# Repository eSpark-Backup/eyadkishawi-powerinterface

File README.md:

# Power and Interface Board Design
#### Client Name: Eyad Kishawi

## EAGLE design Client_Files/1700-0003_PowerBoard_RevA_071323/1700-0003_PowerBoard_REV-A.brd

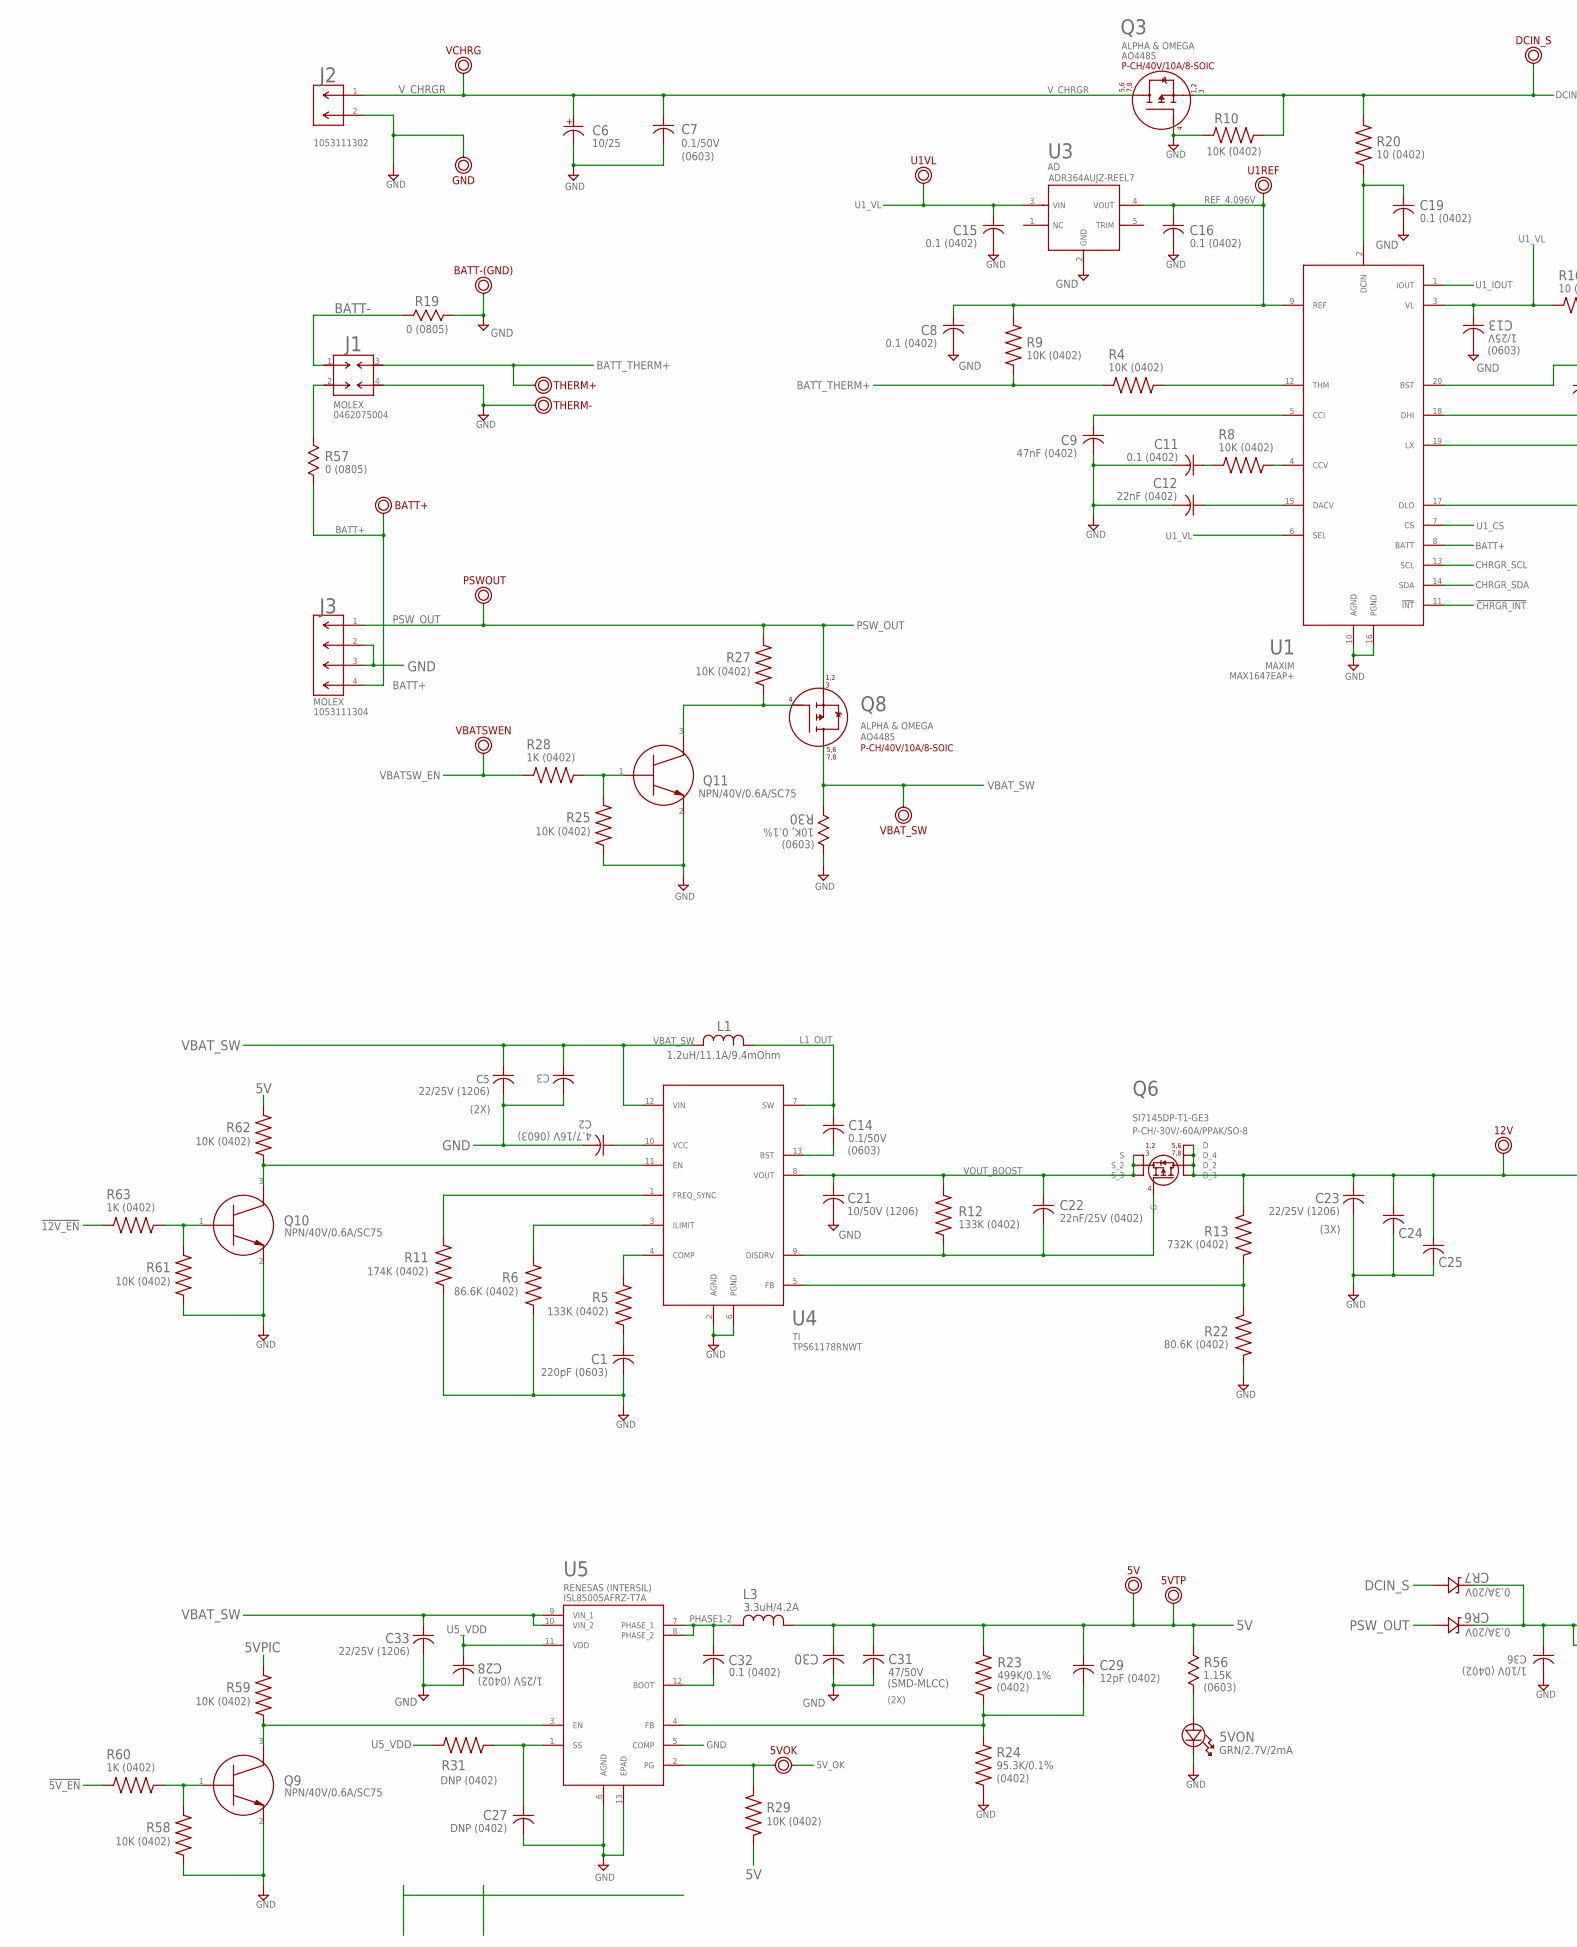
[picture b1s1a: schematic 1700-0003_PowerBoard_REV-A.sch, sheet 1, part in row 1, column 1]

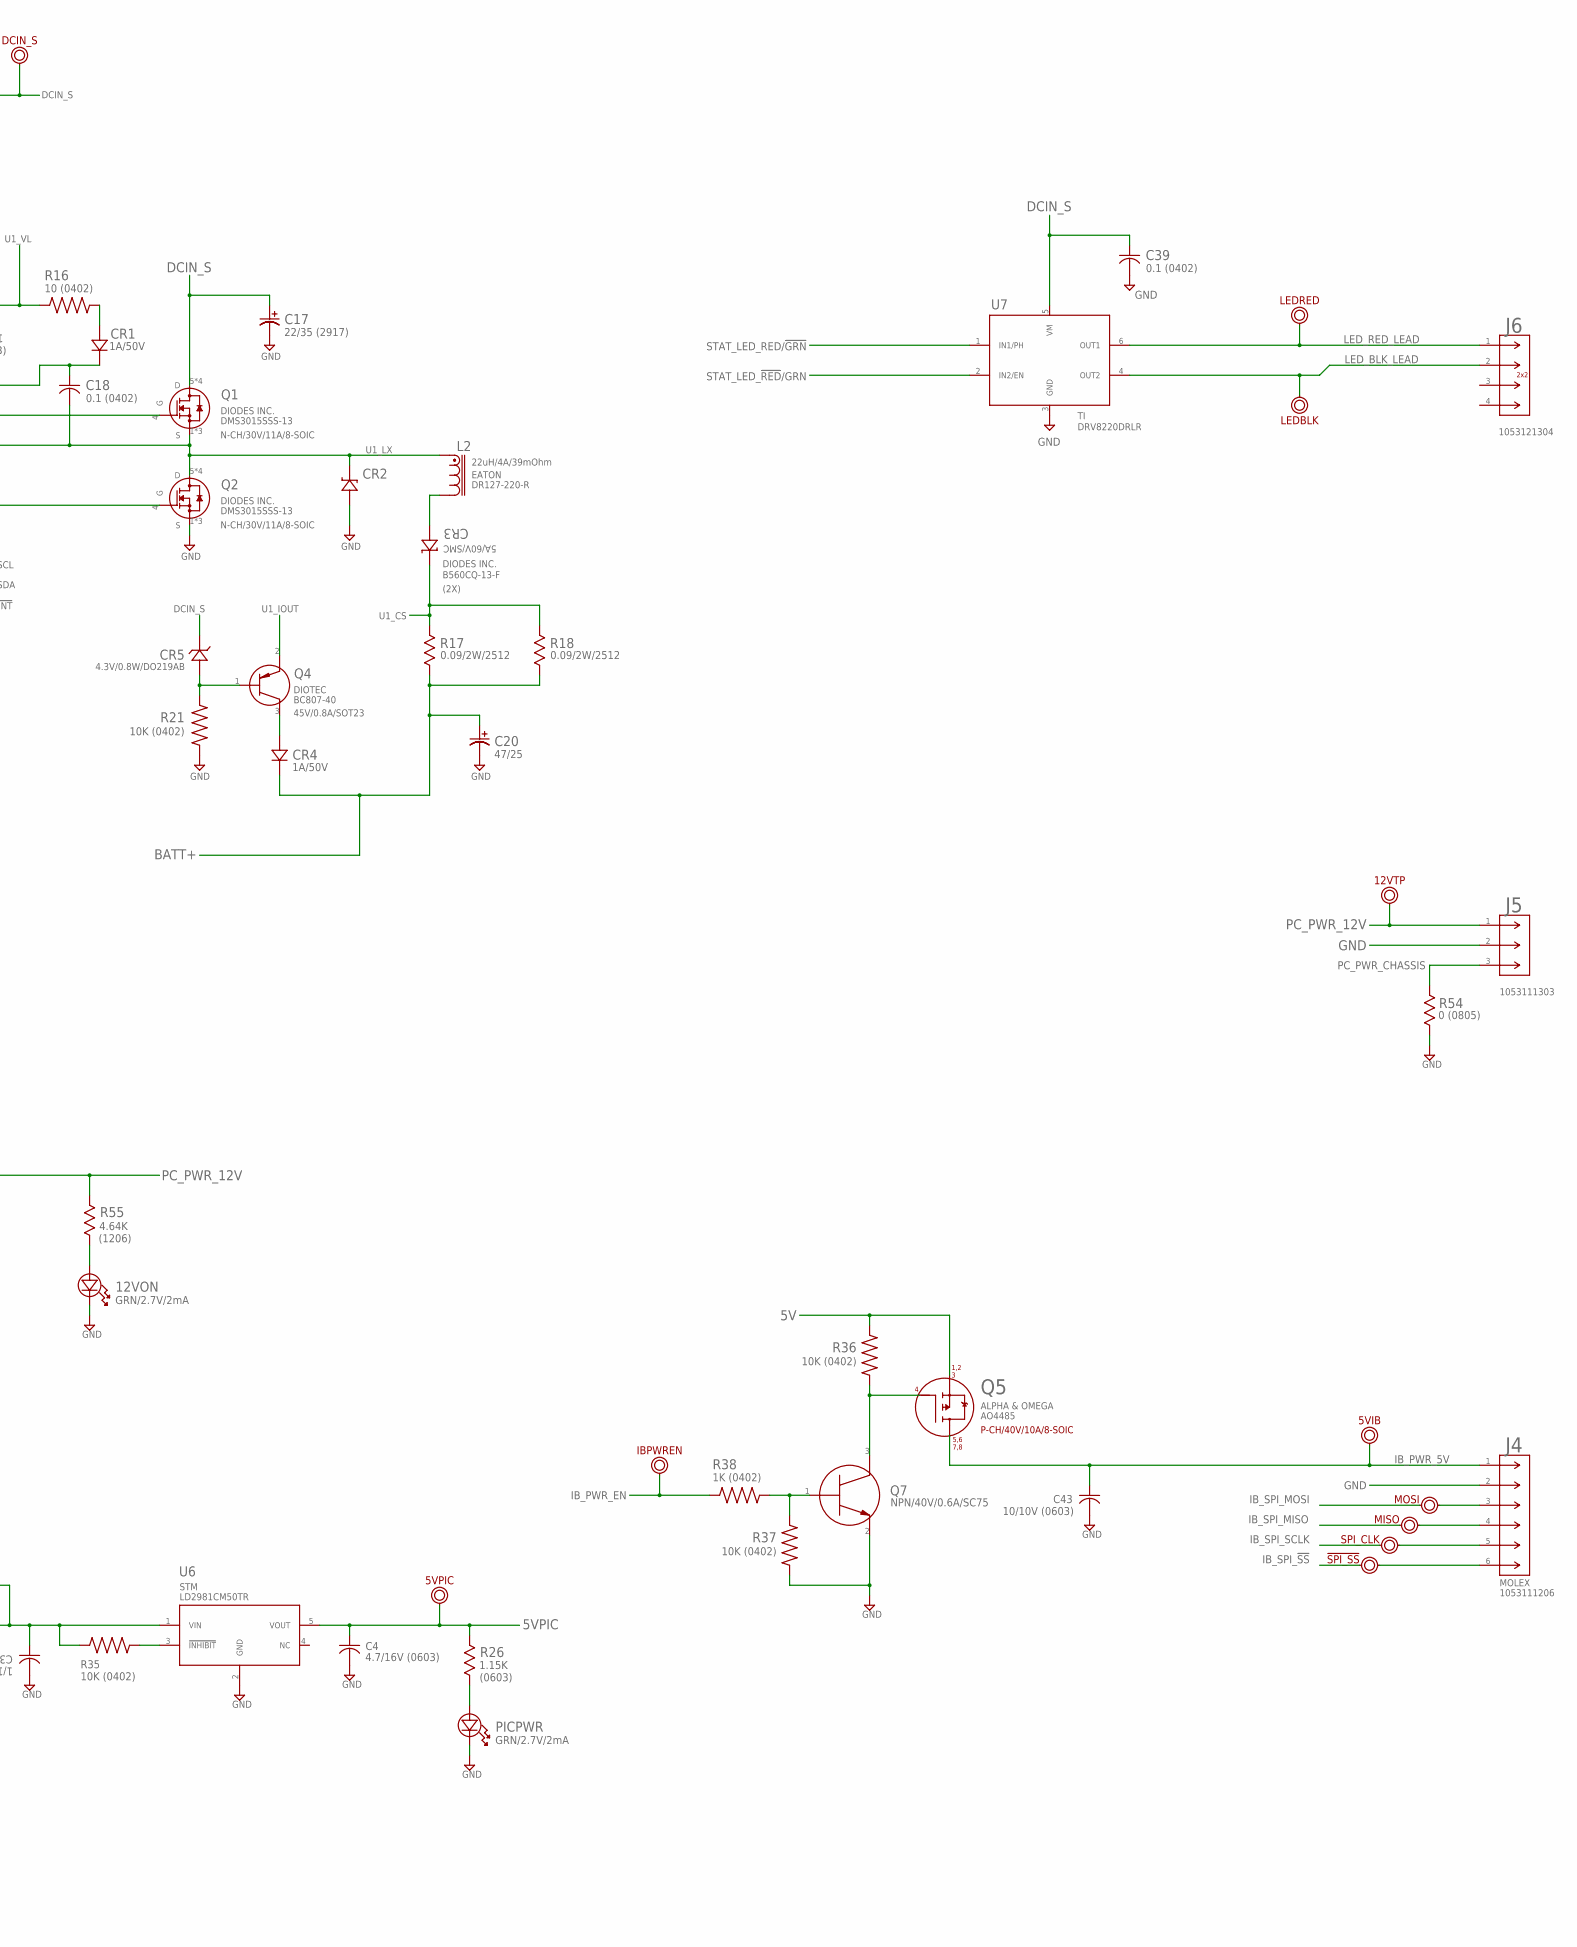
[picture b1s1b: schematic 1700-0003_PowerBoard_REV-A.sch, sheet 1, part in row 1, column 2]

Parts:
5V, 5VPIC, 12V: TST_POINT_PTH_042-OCT
5VIB, 5VTP, 12VTP: TST_POINT_PTH_20X40MIL
5VOK: TST_POINT_PTH_20X40MIL_2PIN
5VON, 12VON: GRN/2.7V/2mA; LED_DIALIGHT_598_DIA
!SPI_SS!: TST_POINT_PTH_042_2PIN; TST_POINT_PTH_042-OCT_2PIN; PART_DESC PCB feature, test point, ID 42mil, OD 7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
BATT+: TST_POINT_PTH_042-OCT
BATT-(GND): TST_POINT_PTH_042-OCT
C1: 220pF (0603); CAP_C1608_TDK; MANUFACTURER_PART_NUMBER CL10C221JB8NNNC
C2, C4: 4.7/16V (0603); CAP_C1608_TDK; MANUFACTURER_PART_NUMBER GRM188Z71C475KE21D
C3, C5, C33: 22/25V (1206); CAP_CL31_SAM
C6: 10/25; CAP_AFK106M25B12T-F_CND-L
C7, C14: 0.1/50V; CAP_C1608_TDK; MANUFACTURER_PART_NUMBER CL10B104KB8NNNC
C8, C11, C15, C16, C18, C19, C32, C39: 0.1 (0402); G-155_MUR
C9: 47nF (0402); G-155_MUR; MANUFACTURER_PART_NUMBER C0402C473K3REC7867
C12: 22nF (0402); G-155_MUR; MANUFACTURER_PART_NUMBER C0402C223K5REC7411
C13: 1/25V; CAP_C1608_TDK; MANUFACTURER_PART_NUMBER CL10B105KA8NNNC
C17: 22/35 (2917); CAPMP7.6X4.3_3.1N_KEM
C20: 47/25; CAPMP7.6X4.3_3.1N_KEM
C21: 10/50V (1206); CAP_CL31_SAM; MANUFACTURER_PART_NUMBER CL31B106KBHNNNE
C22: 22nF/25V (0402); G-155_MUR; MANUFACTURER_PART_NUMBER GRM155R71E223KA61D
C23, C24, C25: 22/25V (1206); CAP_CL31_SAM; MANUFACTURER_PART_NUMBER GCM31CC81E226KE11L
C27: DNP (0402); G-155_MUR; PART_DESC --- DO NOT POPULATE ---
C28: 1/25V (0402); G-155_MUR; MANUFACTURER_PART_NUMBER GRM155R61E105KA12D
C29: 12pF (0402); G-155_MUR; MANUFACTURER_PART_NUMBER C0402C120K5RAC7867
C30: 47/50V (MLCC-SMD); CAP_CKG57N_TDK
C31: 47/50V; CAP_CKG57N_TDK
C36: 1/10V (0402); G-155_MUR; MANUFACTURER_PART_NUMBER GRM155C81C225ME15D
C43: 10/10V (0603); CAP_C1608_TDK; MANUFACTURER_PART_NUMBER GRM188D71A106KA73D
CR1, CR4: 1A/50V; SMA_DIO
CR2, CR3: 5A/60V/SMC; CR_0CQ-13-F_DIO
CR5: 4.3V/0.8W/DO219AB; DIO_BZD27C4V3P_VIS
CR6, CR7: 0.3A/20V; USC_TOS
DCIN_S: TST_POINT_PTH_042-OCT
GND: TST_POINT_PTH_042-OCT
IBPWREN: TST_POINT_PTH_042-OCT
J1: MOLEX_MINI-FIT-JR_462075004; MOLEX_462075004
J2: MOLEX_NANO-FIT_1053111302; CON_1053111302_MOL
J3: MOLEX_NANO-FIT_1053111304; CON_1053111304_MOL
J4: MOLEX_1053111206; CON_1053111206_MOL
J5: MOLEX_NANO-FIT_1053111303; CON_1053111303_MOL
J6: CON_MOLEX_NANOFIT_1053121304; CON_1053121304
L1: 1.2uH/11.1A/9.4mOhm; IND_XAL50XX_COC
L2: 22uH/4A/39mOhm; DR127
L3: 3.3uH/4.2A; IND_CB_DRA74
LEDBLK: TST_POINT_PTH_20X40MIL
LEDRED: TST_POINT_PTH_20X40MIL
MISO: TST_POINT_PTH_042_2PIN; TST_POINT_PTH_042-OCT_2PIN; PART_DESC PCB feature, test point, ID 42mil, OD 7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
MOSI: TST_POINT_PTH_042_2PIN; TST_POINT_PTH_042-OCT_2PIN; PART_DESC PCB feature, test point, ID 42mil, OD 7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
PICPWR: GRN/2.7V/2mA; LED_DIALIGHT_598_DIA
PSWOUT: TST_POINT_PTH_042-OCT
Q1, Q2: N-CH/30V/11A/8-SOIC; SOIC127P600X175-8N
Q3, Q5, Q8: P-CH/40V/10A/8-SOIC; SOIC127P600X175-8N
Q4: 45V/0.8A/SOT23; SOT-23-3_DIOTEC
Q6: P-CH/-30V/-60A/PPAK/SO-8; SON8_SI7135DP-T1-GE3_VIS
Q7, Q9, Q10, Q11: NPN/40V/0.6A/SC75; SC-75(SOT-416)_ONSEMI
R4, R8, R9, R10, R21, R25, R27, R29, R35, R36, R37, R58, R59, R61, R62: 10K (0402); RESC1005X35N
R5: 133K (0402); RESC1005X35N; MANUFACTURER_PART_NUMBER RMCF0402FT133K
R6: 86.6K (0402); RESC1005X35N; MANUFACTURER_PART_NUMBER CPF0402B86K6E1
R11: 174K (0402); RESC1005X35N; MANUFACTURER_PART_NUMBER CRCW0402174KFKTD
R12: 133K (0402); RESC1005X35N; MANUFACTURER_PART_NUMBER RC0402FR-07178KL
R13: 732K (0402); RESC1005X35N; MANUFACTURER_PART_NUMBER CRCW0402732KFKED
R16, R20: 10 (0402); RESC1005X35N; MANUFACTURER_PART_NUMBER CRCW040210R0FKEDC
R17, R18: 0.09/2W/2512; RES_2512_TECONN
R19, R54, R57: 0 (0805); STA_HCJ0805_STP
R22: 80.6K (0402); RESC1005X35N; MANUFACTURER_PART_NUMBER CRCW040280K6FKED
R23: 499K/0.1%; RESC1005X35N; MANUFACTURER_PART_NUMBER MCS0402MD4993BE000
R24: 95.3K/0.1%; RESC1005X35N; MANUFACTURER_PART_NUMBER TNPW040295K3BEED
R26, R56: 1.15K; STA_RMCF0603_STP; MANUFACTURER_PART_NUMBER RMCF0603FT1K15
R28, R38, R60, R63: 1K (0402); RESC1005X35N; MANUFACTURER_PART_NUMBER CRCW04021K00FKEDC
R30: 10K, 0.1%; STA_RMCF0603_STP; MANUFACTURER_PART_NUMBER RNCS0603BKE10K0
R31: DNP (0402); RESC1005X35N; MANUFACTURER_PART_NUMBER ---
R55: 4.64K; RC1206N_YAG; MANUFACTURER_PART_NUMBER CRCW12064K64FKEAC
SPI_CLK: TST_POINT_PTH_042_2PIN; TST_POINT_PTH_042-OCT_2PIN; PART_DESC PCB feature, test point, ID 42mil, OD 7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
THERM+: TST_POINT_PTH_042-OCT
THERM-: TST_POINT_PTH_042-OCT
U1: MAX1647EAP+; 21-0056C_20_MXM; PART_DESC IC BATT CHG MULTI-CHEM 20SSOP
U1REF, U1VL: TST_POINT_PTH_20X40MIL
U3: AD_REFERENCE_ADR364AUJZ-REEL7; UJ_5_ADI
U4: REGULATOR_BOOST_TI_TPS61178RNWT; RNW0013A
U5: REGULATOR_BUCK_RENESAS_ISL85005AFRZ-T7A; SON50P300X400X90-13N; PART_DESC Buck Switching Regulator IC Positive Ad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
U6: IC_LDO_STM_LD2981CM50TR; SOT23-5L_STM
U7: IC_H-BRIDGE_TI_DRV8220DRLR; SOT5X3-6_DRL_TEX
VBATSWEN: TST_POINT_PTH_042-OCT
VBAT_SW: TST_POINT_PTH_042-OCT
VCHRG: TST_POINT_PTH_042-OCT; PART_DESC PCB feature, test point, ID 42mil, OD 7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

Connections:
5V: 5V.P$1, 5VTP.P$1, C29.1, C30.1, C31.1, L3.1, Q5.1 (S), Q5.2 (S), Q5.3 (S), R23.1, R29.1, R36.2, R56.2, R62.2; also elsewhere on the board
5VPIC: 5VPIC.P$1, C4.1, R26.2, R59.2, U6.5 (VOUT); also elsewhere on the board
5V_OK: 5VOK.P$1, 5VOK.P$2, R29.2, U5.2 (PG); also elsewhere on the board
!5V_EN!: R60.1; also elsewhere on the board
!12V_EN!: R63.1; also elsewhere on the board
!CHRGR_INT!: U1.11 (!INT); also elsewhere on the board
$N36: C36.1, CR6.1 (K), CR7.1 (K), R35.2, U6.1 (VIN)
$N99: J1.2, R57.2
BATT+: BATT+.P$1, C20.1, CR4.1, J3.4, R17.2, R18.2, R57.1, U1.8 (BATT)
BATT-: J1.1, R19.2
BATT_THERM+: J1.3, R4.1, R9.2, THERM+.P$1
CHRGR_SCL: U1.13 (SCL); also elsewhere on the board
CHRGR_SDA: U1.14 (SDA); also elsewhere on the board
DCIN_S: C17.1, C39.1, CR5.2 (K), CR7.2 (A), DCIN_S.P$1, Q1.5 (D), Q1.6 (D), Q1.7 (D), Q1.8 (D), Q3.1 (S), Q3.2 (S), Q3.3 (S), R10.2, R20.2, U7.5 (VM); also elsewhere on the board
GND: 5VON.1, 12VON.1, BATT-(GND).P$1, C1.2, C2.2, C3.2, C4.2, C5.2, C6.2, C7.2, C8.2, C9.2, C11.2, C12.2, C13.2, C15.2, C16.2, C17.2, C19.2, C20.2, C21.2, C23.2, C24.2, C25.2, C27.2, C28.2, C30.2, C31.2, C33.2, C36.2, C39.2, C43.2, CR2.1 (A), GND.P$1, J1.4, J2.2, J3.2, J3.3, J4.2, J5.2, PICPWR.1, Q2.1 (S), Q2.2 (S), Q2.3 (S), Q3.4 (G), Q7.2 (E), Q9.2 (E), Q10.2 (E), Q11.2 (E), R6.2, R10.1, R11.2, R19.1, R21.2, R22.2, R24.2, R25.1, R30.2, R37.1, R54.2, R58.1, R61.1, THERM-.P$1, U1.10 (AGND), U1.16 (PGND), U3.2 (GND), U4.2 (AGND), U4.6 (PGND), U5.5 (COMP), U5.6 (AGND), U5.13 (EPAD), U6.2 (GND), U7.3 (GND); also elsewhere on the board
IB_PWR_5V: 5VIB.P$1, C43.1, J4.1, Q5.5 (D), Q5.6 (D), Q5.7 (D), Q5.8 (D)
IB_PWR_EN: IBPWREN.P$1, R38.1; also elsewhere on the board
IB_SPI_!SS: !SPI_SS!.P$1, !SPI_SS!.P$2, J4.6; also elsewhere on the board
IB_SPI_MISO: J4.4, MISO.P$1, MISO.P$2; also elsewhere on the board
IB_SPI_MOSI: J4.3, MOSI.P$1, MOSI.P$2; also elsewhere on the board
IB_SPI_SCLK: J4.5, SPI_CLK.P$1, SPI_CLK.P$2; also elsewhere on the board
L1_OUT: C14.1, L1.1, U4.7 (SW)
LED_BLK_LEAD: J6.2, LEDBLK.P$1, U7.4 (OUT2)
LED_RED_LEAD: J6.1, LEDRED.P$1, U7.6 (OUT1)
unnamed: R5.1, U4.4 (COMP)
unnamed: C19.1, R20.1, U1.2 (DCIN)
unnamed: Q1.4 (G), U1.18 (DHI)
unnamed: C1.1, R5.2
unnamed: R4.2, U1.12 (THM)
unnamed: R6.1, U4.3 (ILIMIT)
unnamed: C2.1, U4.10 (VCC)
unnamed: R11.1, U4.1 (FREQ_SYNC)
unnamed: C9.1, U1.5 (CCI)
unnamed: R8.2, U1.4 (CCV)
unnamed: C11.1, R8.1
unnamed: C12.1, U1.15 (DACV)
unnamed: CR4.2, Q4.3 (C)
unnamed: CR1.2, R16.2
unnamed: Q2.4 (G), U1.17 (DLO)
unnamed: C18.1, CR1.1, U1.20 (BST)
unnamed: CR3.1 (A), L2.2
unnamed: C14.2, U4.13 (BST)
unnamed: C22.2, Q6.4 (G), R12.2, U4.9 (DISDRV)
unnamed: CR5.1 (A), Q4.1 (B), R21.1
unnamed: Q8.4 (G), Q11.3 (C), R27.1
unnamed: C27.1, R31.2, U5.1 (SS)
unnamed: R13.2, R22.1, U4.5 (FB)
unnamed: C32.2, U5.12 (BOOT)
unnamed: C29.2, R23.2, R24.1, U5.4 (FB)
unnamed: 5VON.2, R56.1
unnamed: R35.1, U6.3 (!INHIBIT!)
unnamed: Q11.1 (B), R25.2, R28.2
unnamed: Q5.4 (G), Q7.3 (C), R36.1
unnamed: Q7.1 (B), R37.2, R38.2
unnamed: 12VON.2, R55.2
unnamed: PICPWR.2, R26.1
unnamed: Q9.1 (B), R58.2, R60.2
unnamed: Q9.3 (C), R59.1, U5.3 (EN)
unnamed: Q10.3 (C), R62.1, U4.11 (EN)
unnamed: Q10.1 (B), R61.2, R63.2
PC_PWR_12V: 12V.P$1, 12VTP.P$1, C23.1, C24.1, C25.1, J5.1, Q6.5 (D_3), Q6.6 (D_2), Q6.7 (D_4), Q6.8 (D), R13.1, R55.1; also elsewhere on the board
PC_PWR_CHASSIS: J5.3, R54.1
PHASE1-2: C32.1, L3.2, U5.7 (PHASE_1), U5.8 (PHASE_2)
PSW_OUT: CR6.2 (A), J3.1, PSWOUT.P$1, Q8.1 (S), Q8.2 (S), Q8.3 (S), R27.2; also elsewhere on the board
REF_4.096V: C8.1, C16.1, R9.1, U1.9 (REF), U1REF.P$1, U3.4 (VOUT)
STAT_LED_!RED!/GRN: U7.2 (IN2/EN); also elsewhere on the board
STAT_LED_RED/!GRN!: U7.1 (IN1/PH); also elsewhere on the board
U1_CS: CR3.2 (K), R17.1, R18.1, U1.7 (CS)
U1_IOUT: Q4.2 (E), U1.1 (IOUT)
U1_LX: C18.2, CR2.2 (K), L2.1, Q1.1 (S), Q1.2 (S), Q1.3 (S), Q2.5 (D), Q2.6 (D), Q2.7 (D), Q2.8 (D), U1.19 (LX)
U1_VL: C13.1, C15.1, R16.1, U1.3 (VL), U1.6 (SEL), U1VL.P$1, U3.3 (VIN)
U5_VDD: C28.1, R31.1, U5.11 (VDD)
VBATSW_EN: R28.1, VBATSWEN.P$1; also elsewhere on the board
VBAT_SW: C3.1, C5.1, C33.1, L1.2, Q8.5 (D), Q8.6 (D), Q8.7 (D), Q8.8 (D), R30.1, U4.12 (VIN), U5.9 (VIN_1), U5.10 (VIN_2), VBAT_SW.P$1
VOUT_BOOST: C21.1, C22.1, Q6.1 (S_3), Q6.2 (S_2), Q6.3 (S), R12.1, U4.8 (VOUT)
V_CHRGR: C6.1, C7.1, J2.1, Q3.5 (D), Q3.6 (D), Q3.7 (D), Q3.8 (D), VCHRG.P$1

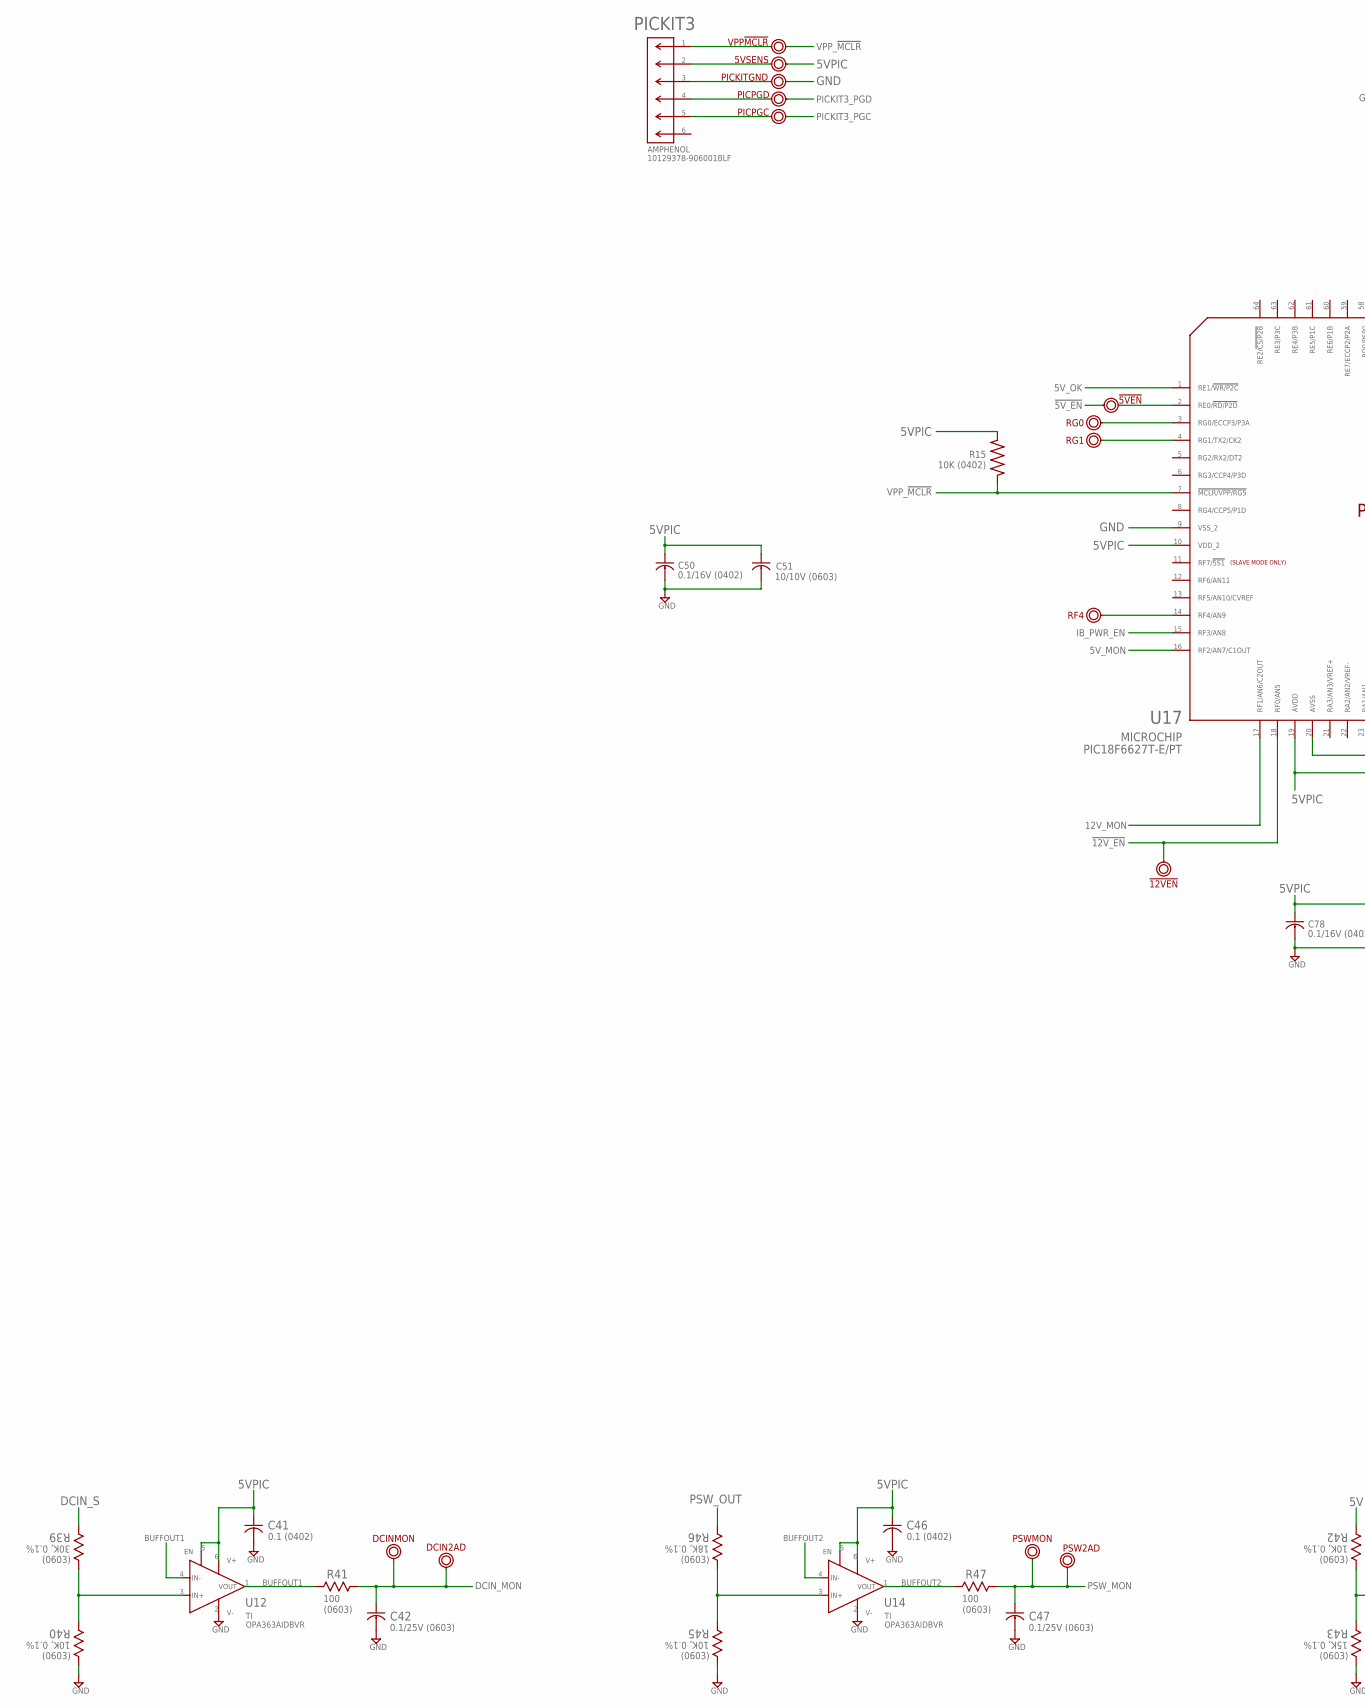
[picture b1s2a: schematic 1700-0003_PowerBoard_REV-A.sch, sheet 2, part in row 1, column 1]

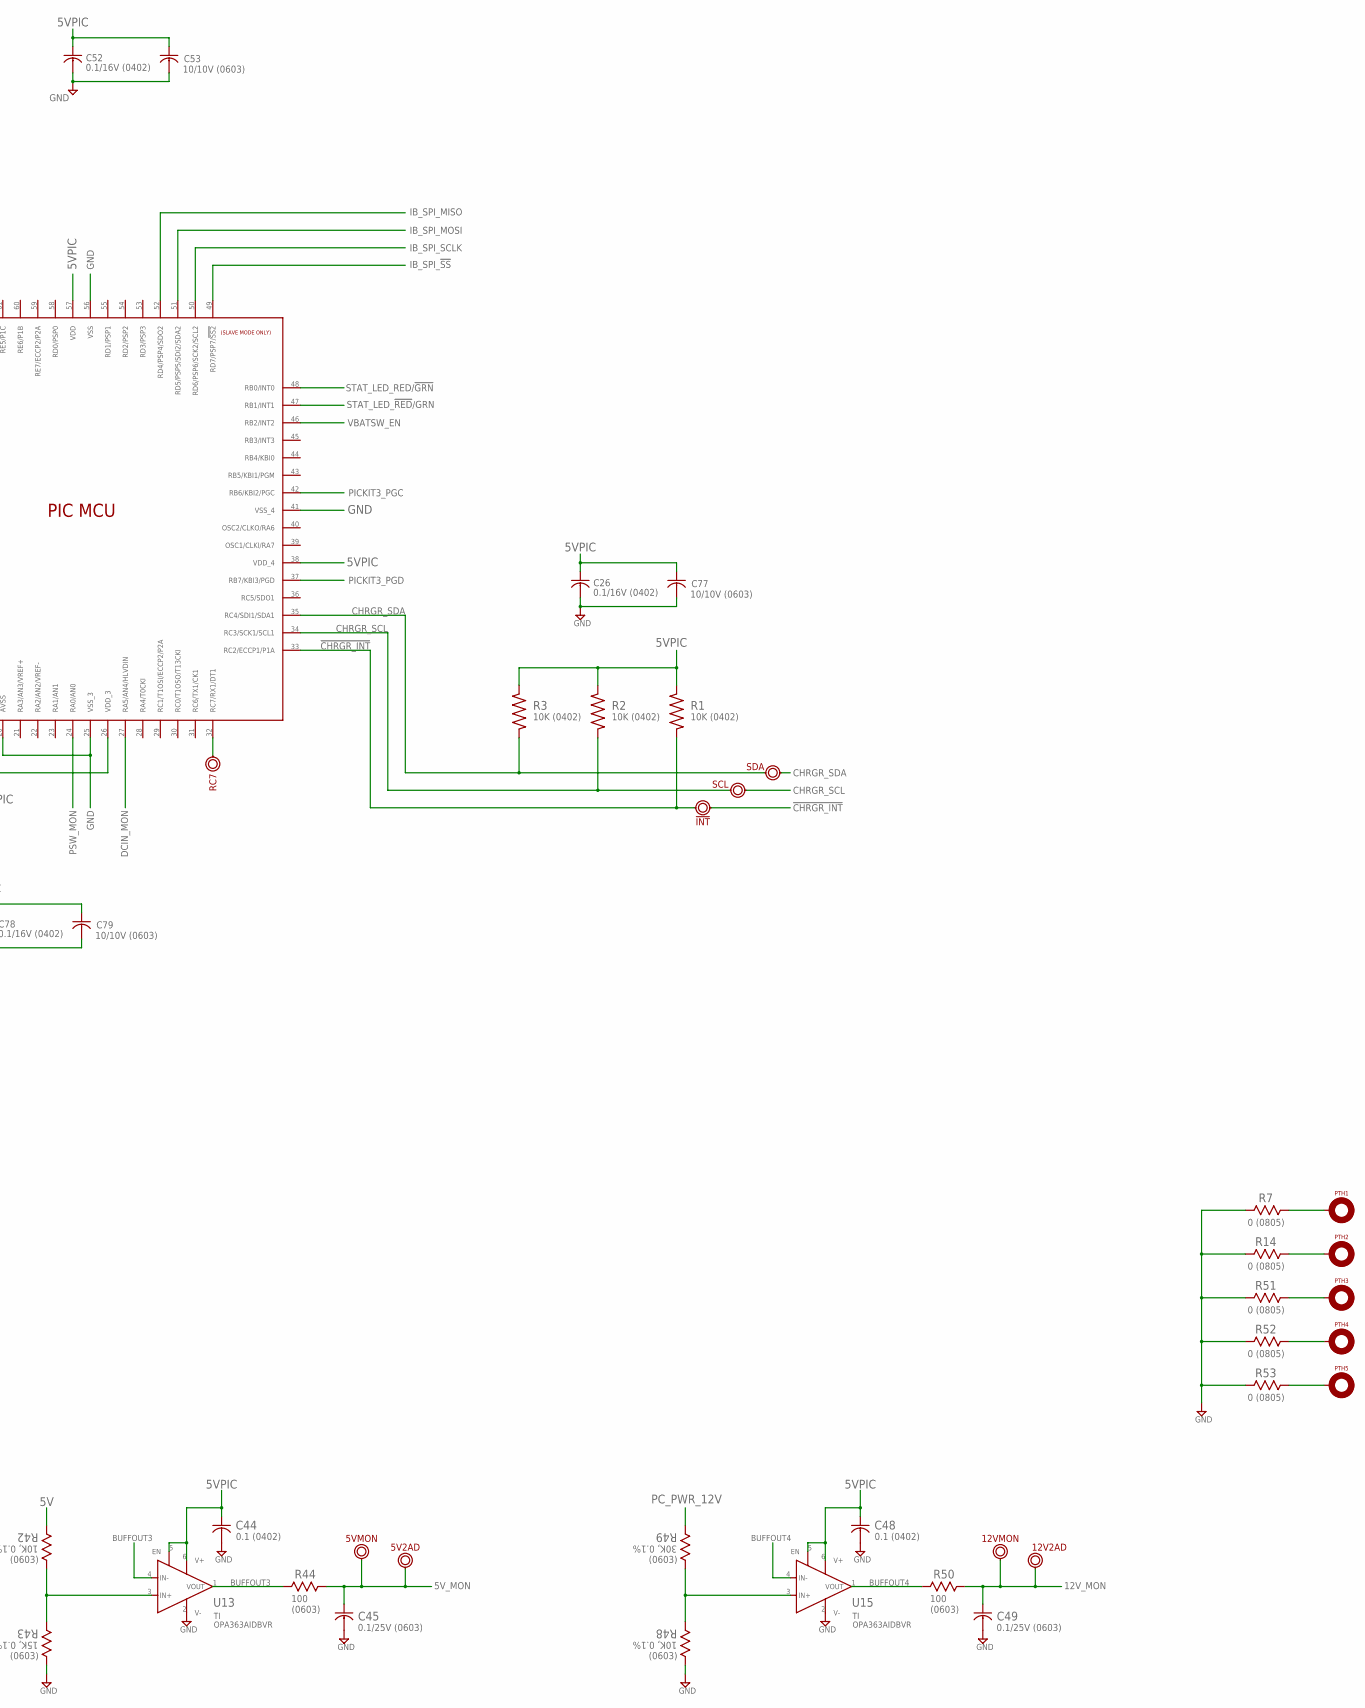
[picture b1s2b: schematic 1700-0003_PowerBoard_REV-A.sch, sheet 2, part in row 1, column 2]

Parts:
5V2AD, 12V2AD: TST_POINT_PTH_20X40MIL
5VMON, 12VMON: TST_POINT_PTH_042-OCT
5VSENS: TST_POINT_PTH_20X40MIL_2PIN
!5VEN: TST_POINT_PTH_20X40MIL_2PIN
!12VEN: TST_POINT_PTH_20X40MIL
!INT!: TST_POINT_PTH_20X40MIL_2PIN
C26, C50, C52, C78: 0.1/16V (0402); G-155_MUR
C41, C44, C46, C48: 0.1 (0402); G-155_MUR
C42, C45, C47, C49: 0.1/25V (0603); CAP_C1608_TDK; MANUFACTURER_PART_NUMBER C0603C104K3RAC7867
C51, C53, C77, C79: 10/10V (0603); CAP_C1608_TDK; MANUFACTURER_PART_NUMBER GRM188D71A106KA73D
DCIN2AD: TST_POINT_PTH_20X40MIL
DCINMON: TST_POINT_PTH_042-OCT
PICKIT3: CON_6POS_VERT-HDR_AMPH_10129378-906001; CON6_1X6_VERT-HDR
PICKITGND: TST_POINT_PTH_20X40MIL_2PIN
PICPGC: TST_POINT_PTH_20X40MIL_2PIN
PICPGD: TST_POINT_PTH_20X40MIL_2PIN
PSW2AD: TST_POINT_PTH_20X40MIL
PSWMON: TST_POINT_PTH_042-OCT
PTH1, PTH2, PTH3, PTH4, PTH5: PTH_4-40
R1, R2, R3, R15: 10K (0402); RESC1005X35N
R7, R14, R51, R52, R53: 0 (0805); STA_HCJ0805_STP
R39, R49: 30K, 0.1%; STA_RMCF0603_STP; MANUFACTURER_PART_NUMBER CPF0603B30KE1
R40, R42, R45, R48: 10K, 0.1%; STA_RMCF0603_STP; MANUFACTURER_PART_NUMBER RNCS0603BKE10K0
R41, R44, R47, R50: 100; STA_RMCF0603_STP; MANUFACTURER_PART_NUMBER CPF0603F100RC1
R43: 15K, 0.1%; STA_RMCF0603_STP; MANUFACTURER_PART_NUMBER CPF0603B15KE1
R46: 18K, 0.1%; STA_RMCF0603_STP; MANUFACTURER_PART_NUMBER CPF0603B18KE1
RC7: TST_POINT_PTH_042-OCT
RF4: TST_POINT_PTH_042-OCT
RG0, RG1: TST_POINT_PTH_042-OCT
SCL: TST_POINT_PTH_20X40MIL_2PIN
SDA: TST_POINT_PTH_20X40MIL_2PIN
U12, U13, U14, U15: IC_OPAMP_TI_OPA363AIDBVR; DBV6
U17: PIC18F6627T-E/PT; TQFP64_10X10MC_MCH
VPP!MCLR!: TST_POINT_PTH_20X40MIL_2PIN

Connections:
5V: R42.1; also elsewhere on the board
5VPIC: 5VSENS.P$1, 5VSENS.P$2, C26.1, C41.1, C44.1, C46.1, C48.1, C50.1, C51.1, C52.1, C53.1, C77.1, C78.1, C79.1, PICKIT3.2, R1.1, R2.1, R3.1, R15.1, U12.5 (EN), U12.6 (V+), U13.5 (EN), U13.6 (V+), U14.5 (EN), U14.6 (V+), U15.5 (EN), U15.6 (V+), U17.10 (VDD_2), U17.19 (AVDD), U17.26 (VDD_3), U17.38 (VDD_4), U17.57 (VDD); also elsewhere on the board
5V_MON: 5V2AD.P$1, 5VMON.P$1, C45.1, R44.2, U17.16 (RF2/AN7/C1OUT)
5V_OK: U17.1 (RE1/!WR/P2C); also elsewhere on the board
12V_MON: 12V2AD.P$1, 12VMON.P$1, C49.1, R50.2, U17.17 (RF1/AN6/C2OUT)
!5V_EN!: !5VEN.P$1, !5VEN.P$2, U17.2 (RE0/!RD/P2D); also elsewhere on the board
!12V_EN!: !12VEN.P$1, U17.18 (RF0/AN5); also elsewhere on the board
!CHRGR_INT!: !INT!.P$2, R1.2, U17.33 (RC2/ECCP1/P1A); also elsewhere on the board
BUFFOUT1: R41.1, U12.1 (VOUT), U12.4 (IN-)
BUFFOUT2: R47.1, U14.1 (VOUT), U14.4 (IN-)
BUFFOUT3: R44.1, U13.1 (VOUT), U13.4 (IN-)
BUFFOUT4: R50.1, U15.1 (VOUT), U15.4 (IN-)
CHRGR_SCL: R2.2, SCL.P$2, U17.34 (RC3/SCK1/SCL1); also elsewhere on the board
CHRGR_SDA: R3.2, SDA.P$2, U17.35 (RC4/SDI1/SDA1); also elsewhere on the board
DCIN_MON: C42.1, DCIN2AD.P$1, DCINMON.P$1, R41.2, U17.27 (RA5/AN4/HLVDIN)
DCIN_S: R39.1; also elsewhere on the board
GND: C26.2, C41.2, C42.2, C44.2, C45.2, C46.2, C47.2, C48.2, C49.2, C50.2, C51.2, C52.2, C53.2, C77.2, C78.2, C79.2, PICKIT3.3, PICKITGND.P$1, PICKITGND.P$2, R7.2, R14.2, R40.2, R43.2, R45.2, R48.2, R51.2, R52.2, R53.2, U12.2 (V-), U13.2 (V-), U14.2 (V-), U15.2 (V-), U17.9 (VSS_2), U17.20 (AVSS), U17.25 (VSS_3), U17.41 (VSS_4), U17.56 (VSS); also elsewhere on the board
IB_PWR_EN: U17.15 (RF3/AN8); also elsewhere on the board
IB_SPI_!SS: U17.49 (RD7/PSP7/!SS2); also elsewhere on the board
IB_SPI_MISO: U17.52 (RD4/PSP4/SDO2); also elsewhere on the board
IB_SPI_MOSI: U17.51 (RD5/PSP5/SDI2/SDA2); also elsewhere on the board
IB_SPI_SCLK: U17.50 (RD6/PSP6/SCK2/SCL2); also elsewhere on the board
unnamed: RG0.P$1, U17.3 (RG0/ECCP3/P3A)
unnamed: RG1.P$1, U17.4 (RG1/TX2/CK2)
unnamed: RF4.P$1, U17.14 (RF4/AN9)
unnamed: R39.2, R40.1, U12.3 (IN+)
unnamed: R42.2, R43.1, U13.3 (IN+)
unnamed: R45.1, R46.2, U14.3 (IN+)
unnamed: R48.1, R49.2, U15.3 (IN+)
unnamed: RC7.P$1, U17.32 (RC7/RX1/DT1)
unnamed: PTH1.P$1, R7.1
unnamed: PTH2.P$1, R14.1
unnamed: PTH3.P$1, R51.1
unnamed: PTH4.P$1, R52.1
unnamed: PTH5.P$1, R53.1
PC_PWR_12V: R49.1; also elsewhere on the board
PICKIT3_PGC: PICKIT3.5, PICPGC.P$1, PICPGC.P$2, U17.42 (RB6/KBI2/PGC)
PICKIT3_PGD: PICKIT3.4, PICPGD.P$1, PICPGD.P$2, U17.37 (RB7/KBI3/PGD)
PSW_MON: C47.1, PSW2AD.P$1, PSWMON.P$1, R47.2, U17.24 (RA0/AN0)
PSW_OUT: R46.1; also elsewhere on the board
STAT_LED_!RED!/GRN: U17.47 (RB1/INT1); also elsewhere on the board
STAT_LED_RED/!GRN!: U17.48 (RB0/INT0); also elsewhere on the board
VBATSW_EN: U17.46 (RB2/INT2); also elsewhere on the board
VPP_!MCLR!: PICKIT3.1, R15.2, U17.7 (!MCLR/VPP/RG5), VPP!MCLR!.P$1, VPP!MCLR!.P$2

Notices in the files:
parts and their libraries:
COPYRIGHT: Copyright (C) 2022 Ultra Librarian. All rights reserved.
COPYRIGHT: Copyright (C) 2023 Ultra Librarian. All rights reserved.
